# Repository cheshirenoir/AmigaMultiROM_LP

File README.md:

# AmigaMultiROM_LP
This is a 4 way Amiga ROM switcher built using a low profile solution. Tested on the Amiga 600.
Built in a similar fashion to the BeeMultiROM (https://ilike8bits.com/2022/08/10/assembling-the-microbee-multirom/). Drop in turned pins. Solder them in using a turned pin socket to keep everything aligned.
Once consrtucted, just the pins off the two turned pins closest to the connector and insulate. (I used nail polish)
There are 3 data pins to select from 4 ROMs and a common.

CC BY SA

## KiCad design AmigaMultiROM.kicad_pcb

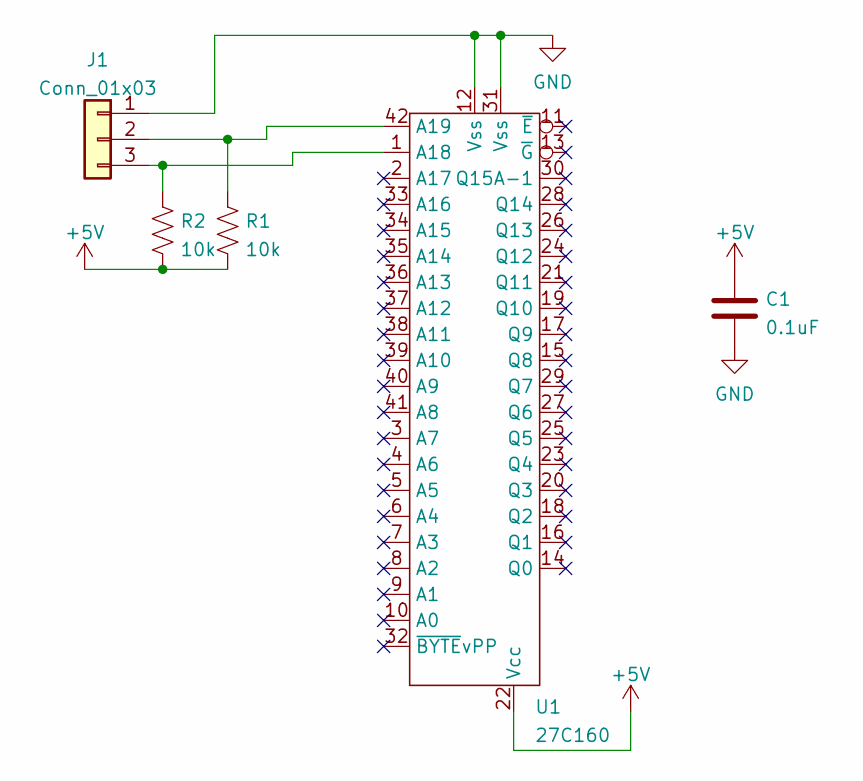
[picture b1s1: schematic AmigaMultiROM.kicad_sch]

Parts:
C1: 0.1uF; C_Disc_D5.1mm_W3.2mm_P5.00mm
J1: Conn_01x03; PinHeader_1x03_P2.54mm_Vertical
R1, R2: 10k; R_Axial_DIN0309_L9.0mm_D3.2mm_P12.70mm_Horizontal
U1: 27C160; DIP-42_604_ELL

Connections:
+5V: C1.1, R1.2, R2.2, U1.22 (Vcc)
GND: C1.2, J1.1, U1.12 (Vss), U1.31 (Vss)
unnamed: J1.2, R1.1, U1.42 (A19)
unnamed: J1.3, R2.1, U1.1 (A18)

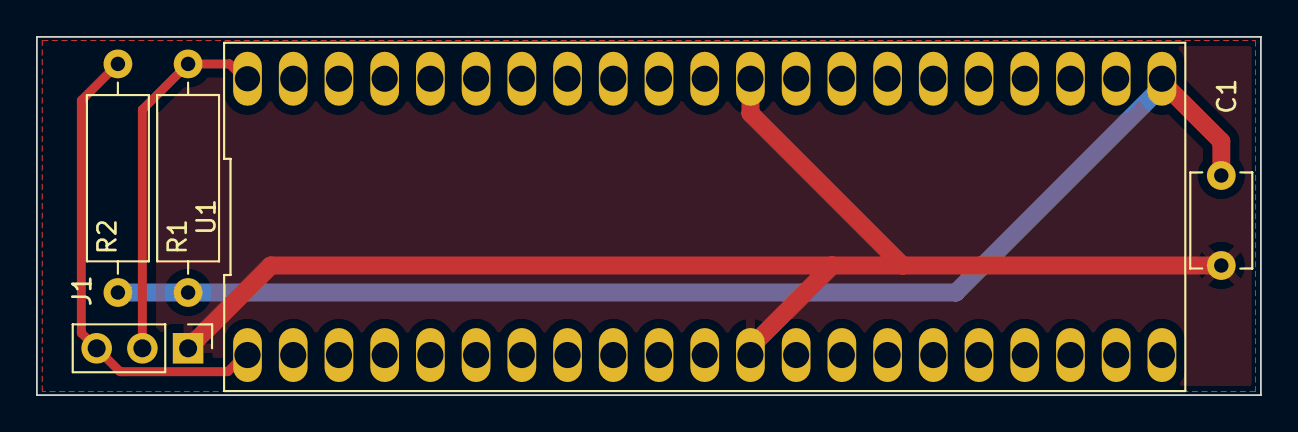
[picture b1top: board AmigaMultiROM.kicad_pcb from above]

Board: 2 copper layers, 68.0 x 19.9 mm, 5 parts (0 on the bottom side), 4 nets.

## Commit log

2022-08-15 Add files via upload
    First version. Tested OK on A600.

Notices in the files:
AmigaMultiROM.kicad_pcb:
By CheshireNoir CC BY SA
